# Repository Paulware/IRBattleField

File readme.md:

IR Battlefield 

Parts

Online videos:
  [Huan Qi Tanks](http://www.youtube.com/watch?v=K-tgRfZG1ec)    
  
Questions/Comments
  paulware@hotmail.com
  
Help with projects
  [I help on Fiverr](http://fiverr.com/paulware/help-with-your-arduino-project)

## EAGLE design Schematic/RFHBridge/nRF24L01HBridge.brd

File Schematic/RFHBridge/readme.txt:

Add a transistor for IR output to increase power from 20ma up...
  A resistor may also be needed
6/5/2013 started testing, seems ok.
6/25/2013 Change D18 to D17 for nRF24L01...Add NPN Transistor for D3 IR output
          Removed extra h-bridge 4pin connector
          IR transmitter
             - Connects to pin that was previously connected to D3...Now transistor
             + Connects to VCC (5V) straight....Is a resistor required?  who knows
             
ReOrdered 6/25/2013

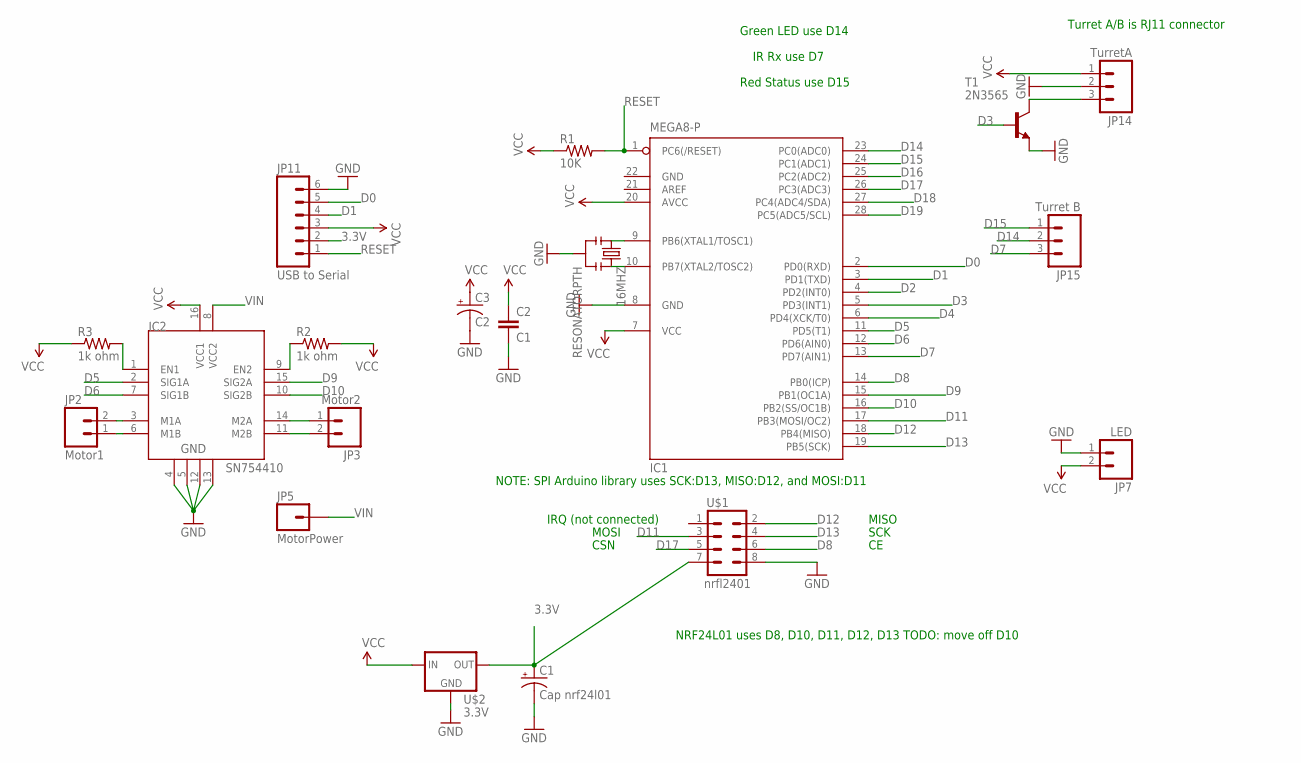
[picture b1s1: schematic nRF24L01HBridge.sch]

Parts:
16MHZ: RESONATORPTH; RESONATOR-PTH
C1: Cap nrf24l01; CPOL-RADIAL-10UF-25V
C2: C1; CAP-PTH-SMALL
C3: C2; CPOL-RADIAL-100UF-25V
IC1: MEGA8-P; DIL28-3
IC2: SN754410; DIP16
JP2: Motor1; 1X02_LOCK
JP3: Motor2; 1X02_LOCK
JP5: MotorPower; 1X01
JP7: LED; 1X02
JP11: USB to Serial; 1X06
JP14: TurretA; 1X03
JP15: Turret B; 1X03
R1: 10K; AXIAL-0.3
R2, R3: 1k ohm; AXIAL-0.3
T1: 2N3565; TO92
U$1: nrfl2401; 2X4
U$2: 3.3V; 78XXL

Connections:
3.3V: C1.1 (+), JP11.2, U$1.7, U$2.GND (OUT)
D0: IC1.2 (PD0(RXD)), JP11.5
D1: IC1.3 (PD1(TXD)), JP11.4
D2: IC1.4 (PD2(INT0))
D3: IC1.5 (PD3(INT1)), T1.2 (B)
D4: IC1.6 (PD4(XCK/T0))
D5: IC1.11 (PD5(T1)), IC2.2 (SIG1A)
D6: IC1.12 (PD6(AIN0)), IC2.7 (SIG1B)
D7: IC1.13 (PD7(AIN1)), JP15.3
D8: IC1.14 (PB0(ICP)), U$1.6
D9: IC1.15 (PB1(OC1A)), IC2.15 (SIG2A)
D10: IC1.16 (PB2(SS/OC1B)), IC2.10 (SIG2B)
D11: IC1.17 (PB3(MOSI/OC2)), U$1.3
D12: IC1.18 (PB4(MISO)), U$1.2
D13: IC1.19 (PB5(SCK)), U$1.4
D14: IC1.23 (PC0(ADC0)), JP15.2
D15: IC1.24 (PC1(ADC1)), JP15.1
D16: IC1.25 (PC2(ADC2))
D17: IC1.26 (PC3(ADC3)), U$1.5
D18: IC1.27 (PC4(ADC4/SDA))
D19: IC1.28 (PC5(ADC5/SCL))
GND: 16MHZ.2, C1.2 (-), C2.2, C3.2 (-), IC1.8 (GND), IC1.22 (GND), IC2.4, IC2.5, IC2.12, IC2.13, JP7.1, JP11.6, JP14.2, T1.3 (E), U$1.8, U$2.IN (GND)
unnamed: 16MHZ.3, IC1.10 (PB7(XTAL2/TOSC2))
unnamed: 16MHZ.1, IC1.9 (PB6(XTAL1/TOSC1))
unnamed: IC2.9 (EN2), R2.P$1 (1)
unnamed: IC2.1 (EN1), R3.P$2 (2)
unnamed: IC2.6 (M1B), JP2.1
unnamed: IC2.3 (M1A), JP2.2
unnamed: IC2.14 (M2A), JP3.1
unnamed: IC2.11 (M2B), JP3.2
unnamed: JP14.3, T1.1 (C)
RESET: IC1.1 (PC6(/RESET)), JP11.1, R1.P$2 (2)
VCC: C2.1, C3.1 (+), IC1.7 (VCC), IC1.20 (AVCC), IC2.16 (VCC1), JP7.2, JP11.3, JP14.1, R1.P$1 (1), R2.P$2 (2), R3.P$1 (1), U$2.OUT (IN)
VIN: IC2.8 (VCC2), JP5.1

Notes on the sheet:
Green LED use D14
IR Rx use D7
Red Status use D15
NRF24L01 uses D8, D10, D11, D12, D13 TODO: move off D10
Turret A/B is RJ11 connector
SCK
MISO
MOSI
CSN
IRQ (not connected)
NOTE: SPI Arduino library uses SCK:D13, MISO:D12, and MOSI:D11

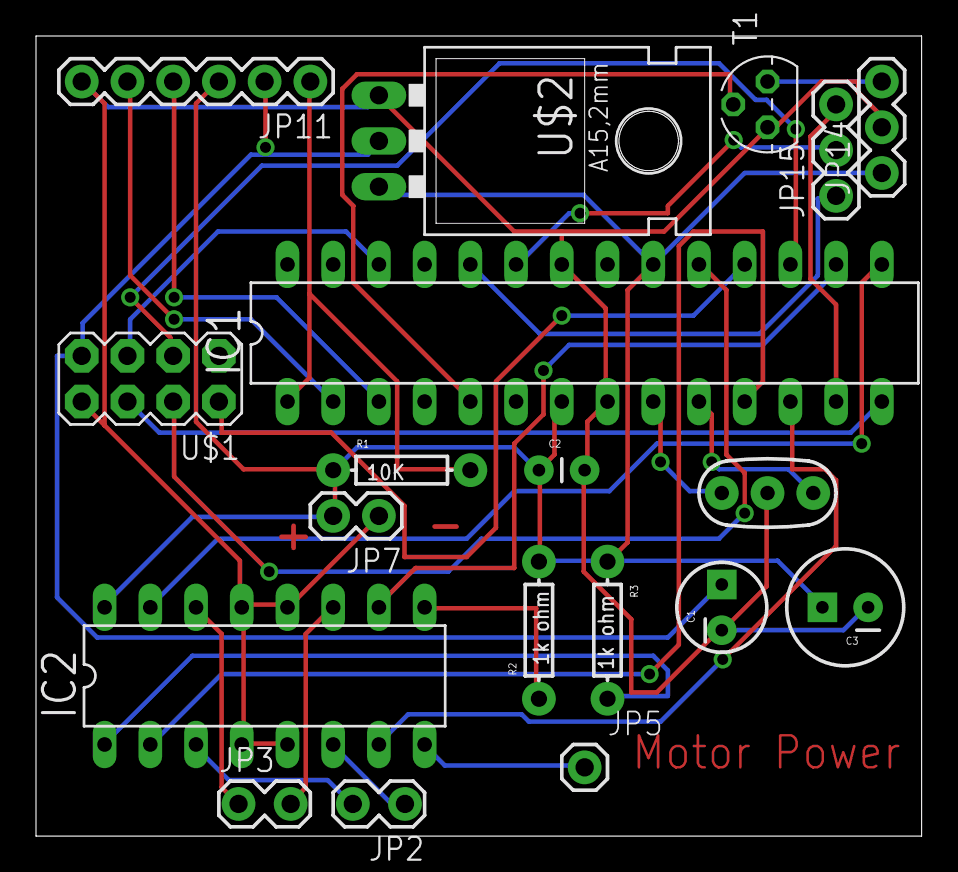
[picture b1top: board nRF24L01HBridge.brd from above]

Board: 2 copper layers, 49.2 x 44.5 mm, 19 parts (0 on the bottom side), 29 nets.

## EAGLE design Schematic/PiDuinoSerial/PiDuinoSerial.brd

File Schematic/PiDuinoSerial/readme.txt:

Wii Mote to Pi to Arduino to nrf24l01 
  transmitter 
3.3V used to power arduino and transmitter
Question: 
   Can I add a I2C Dual Rotary Dip? to select channel
Received 4/12/2013...Not sure what to do with it...Nunchuk better no?

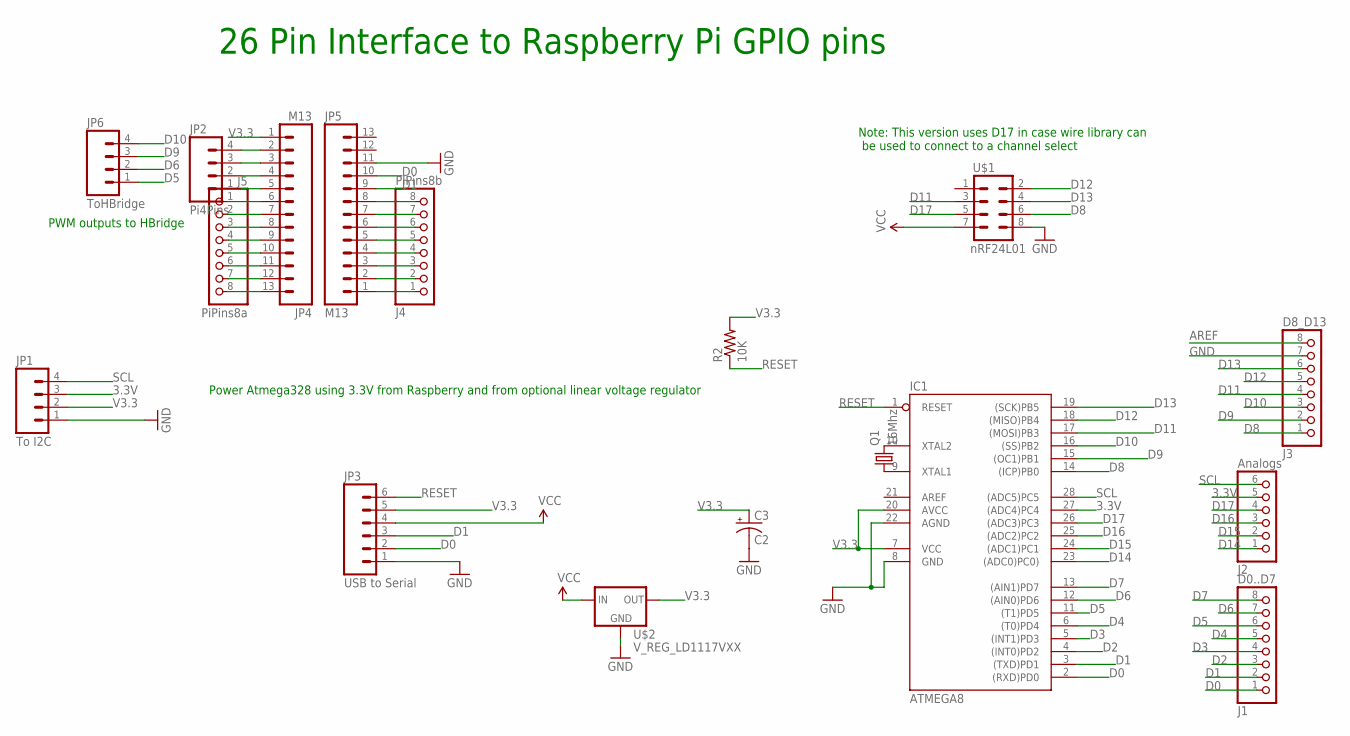
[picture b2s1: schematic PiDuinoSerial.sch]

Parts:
C3: C2; CPOL-RADIAL-100UF-25V
IC1: ATMEGA8; DIL28-3
J1: D0..D7; 1X08
J2: Analogs; 1X06
J3: D8_D13; 1X08
J4: PIPins8b; 1X08
J5: PiPins8a; 1X08
JP1: To I2C; 1X04
JP2: Pi4Pins; 1X04
JP3: USB to Serial; 1X06
JP4, JP5: M13; 1X13
JP6: ToHBridge; 1X04
Q1: 16Mhz; HC49US
R2: 10K; AXIAL-0.3
U$1: nRF24L01; 2X4
U$2: V_REG_LD1117VXX; 78XXL

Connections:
3.3V: IC1.27 ((ADC4)PC4), J2.5, JP1.3
AREF: IC1.21 (AREF), J3.8
D0: IC1.2 ((RXD)PD0), J1.1, JP3.2, JP5.10
D1: IC1.3 ((TXD)PD1), J1.2, JP3.3, JP5.9
D2: IC1.4 ((INT0)PD2), J1.3
D3: IC1.5 ((INT1)PD3), J1.4
D4: IC1.6 ((T0)PD4), J1.5
D5: IC1.11 ((T1)PD5), J1.6, JP6.1
D6: IC1.12 ((AIN0)PD6), J1.7, JP6.2
D7: IC1.13 ((AIN1)PD7), J1.8
D8: IC1.14 ((ICP)PB0), J3.1, U$1.6
D9: IC1.15 ((OC1)PB1), J3.2, JP6.3
D10: IC1.16 ((SS)PB2), J3.3, JP6.4
D11: IC1.17 ((MOSI)PB3), J3.4, U$1.3
D12: IC1.18 ((MISO)PB4), J3.5, U$1.2
D13: IC1.19 ((SCK)PB5), J3.6, U$1.4
D14: IC1.23 ((ADC0)PC0)), J2.1
D15: IC1.24 ((ADC1)PC1), J2.2
D16: IC1.25 ((ADC2)PC2), J2.3
D17: IC1.26 ((ADC3)PC3), J2.4, U$1.5
GND: C3.2 (-), IC1.8 (GND), IC1.22 (AGND), J3.7, JP1.1, JP3.1, JP5.11, U$1.8, U$2.IN (GND)
unnamed: IC1.10 (XTAL2), Q1.2
unnamed: IC1.9 (XTAL1), Q1.1
unnamed: J4.1, JP5.1
unnamed: J4.2, JP5.2
unnamed: J4.3, JP5.3
unnamed: J4.4, JP5.4
unnamed: J4.5, JP5.5
unnamed: J4.6, JP5.6
unnamed: J4.7, JP5.7
unnamed: J4.8, JP5.8
unnamed: J5.1, JP4.6
unnamed: J5.2, JP4.7
unnamed: J5.3, JP4.8
unnamed: J5.4, JP4.9
unnamed: J5.5, JP4.10
unnamed: J5.6, JP4.11
unnamed: J5.7, JP4.12
unnamed: J5.8, JP4.13
unnamed: JP2.1, JP4.5
unnamed: JP2.2, JP4.4
unnamed: JP2.3, JP4.3
unnamed: JP2.4, JP4.2
RESET: IC1.1 (RESET), JP3.6, R2.P$1 (1)
SCL: IC1.28 ((ADC5)PC5), J2.6, JP1.4
V3.3: C3.1 (+), IC1.7 (VCC), IC1.20 (AVCC), JP1.2, JP3.5, JP4.1, R2.P$2 (2), U$2.GND (OUT)
VCC: JP3.4, U$1.7, U$2.OUT (IN)

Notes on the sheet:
26 Pin Interface to Raspberry Pi GPIO pins
Power Atmega328 using 3.3V from Raspberry and from optional linear voltage regulator
PWM outputs to HBridge
Note: This version uses D17 in case wire library can be used to connect to a channel select

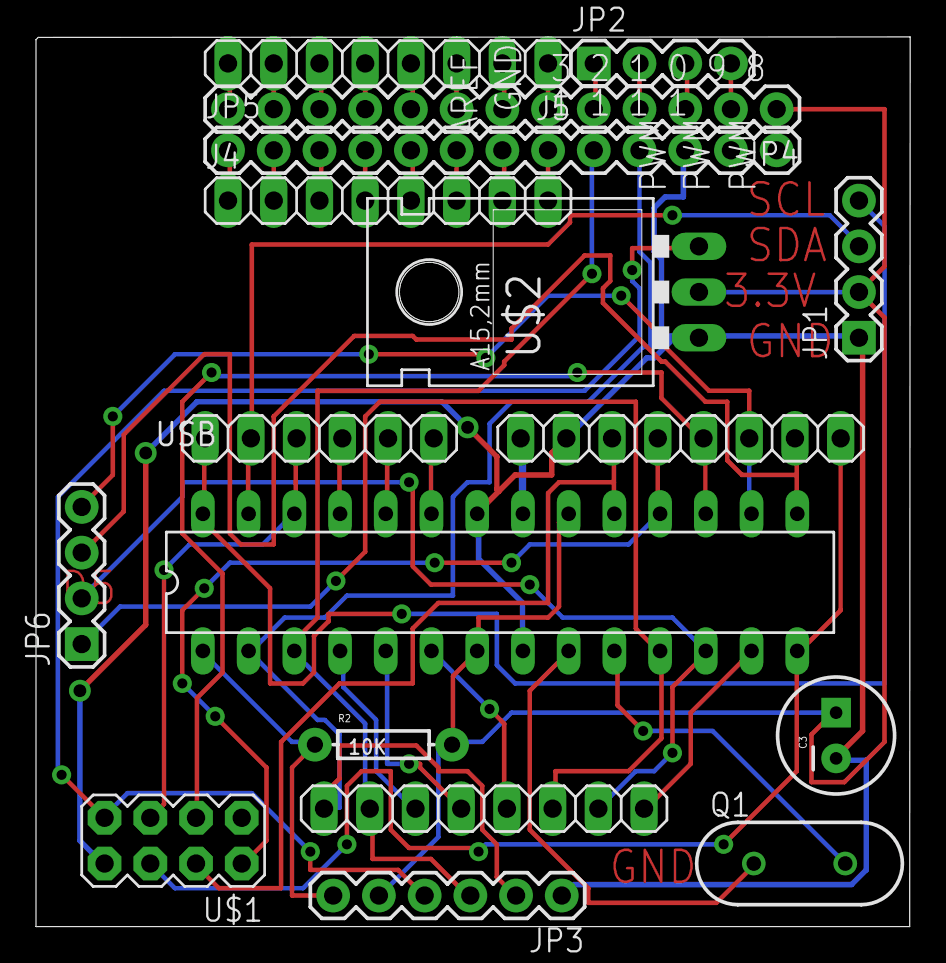
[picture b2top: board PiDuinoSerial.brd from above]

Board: 2 copper layers, 48.6 x 49.4 mm, 17 parts (0 on the bottom side), 47 nets.

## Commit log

2013-02-14 v.01
    Added schematic for receiver
2013-02-14 v.02
    update to readme
2013-02-14 v0.03
    update readme
2013-03-14 v0.04
    Added PiMoteCheck interfacing arduino to Raspberry pi
2014-06-11 V0.05
    Added Android java source code

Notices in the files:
parts and their libraries:
SparkFun-Connectors: Licensing: CC v3.0 Share-Alike You are welcome to use this library for commercial purposes.
